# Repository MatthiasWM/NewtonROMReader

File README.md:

# NewtonROMReader

This archive contains the PCB layout and firmware source code for my Apple 
Newton MessagePad ROM board reader/programmer.

The Newton ROM Reader reads the contents of Apple MessagePad MP2x00 ROM
boards. Besides the well known US and German ROM, this programmer can read 
prototype ROM boards for further research.

Using the alternative Flash ROM Board, the ROM Reader can also program the
Flash chips and create new ROM Boards with patched or alternative 
operating systems. 

## CAUTION

 - Use an original Arduino Due. Do *NOT* use a Mega 2560!
 - Never insert or remove the ROM card while the programmer is powered!
 - All operations are final! There is no undo! There is no confirmation.

## Reader/Programmer

Assembling the Programmer requires some advanced soldering skills. The pin 
headers must be soldered around the outside of the board facing down. They 
must be flush with the PCB on the top, or the ROM board will not fit.

The SD Card connector is soldered to the underside of the board. The top
of the connector should be insulated using an ample amount of tape, avoiding
a short circuit with header pins on the Arduino. ALternatively, the colliding
pins on the Arduino board can be cut off.

The DIMM memory socket is more difficult to solder. The pin pitch is relatively
small. To make sure that the soldering is correct, the first tool to run
in the Programmer should be the short circuit test.

The last solder part is easy, but must not be forgotten. It's a jumper that 
sets the power to 3.2V. Connect the two eyes marked with an asterisk (*).

```
:
:   Lower left corner of the PCB
|
| ooo ooo
| ooo **o
|     ...... ........
+--------------------- - -
``` 

The Programmer board should be mounted on an Arduino Due. It *MUST NOT* be 
used with an Arduino Mega 1280/2560. The Mega runs at 5V and will likely
destroy any ROM, Flash, or SD card inserted into the Programmer. The Due runs
at the required 3.2V. If the large USB-A port of the Arduino blocks access to 
the SD Card slot, you have the wrong board!

The Programmer communicates with the user via USB connection to the Programming
port. No extra power connection is required. There is no extra software for
the Programmer. Users must use a serial terminal program to connect via the 
Programming USB port (57600 bps/baud 8N1).

## Firmware Source Code

The source code comes as an Arduino sketch `.ino` file and a number of 
additional source and header files. The "SdFat" library by Bill Greimann must be 
installed within the Arduino system `Tools > Manage Libraries...`.

Load the `.ino` file and set the board to `Arduino Due (Programming Port)`, 
then choose the right port from the `Tools > Port` menu.

Open the serial monitor `Tools > Serial Monitor` and press `Ctrl-U` to upload
the firmware to the Programmer.  

## PCB Layout

The Programmer PCB was designed with Eagle CAD 7.7.0 Stadard Edition. It's a
two layer board with no exeptional requirements.

The SO-DIMM 72 modules are not very common anymore and are somewhat hard to 
find. The SD Card socket is a standard SMD part. Pin headers should be 
square shaped to fit the Arduino receptacle well.

## Usage

The Programmer writes a 90's style menu over the USB serial port connection.
Functions can be selected by typing the command key and Return. 

 - `h`: Check all connectors on the board for short circuits. This tool helps
        verifying that there are no bridges in the SO DIMM connector soldering.
        *Never run this command with a ROM board or SD Card inserted!*
 - `0`: Select the ROM area from 0x00000000 to 0x00800000 which corresponds
        to the regular ROM and Apple system ROM extension (REx).
 - `1`: This page can be programmed with an extension block of up to 8MB.
 - `2`, `3`: Experimental blocks. These should be mapped to 0x10000000 and 
        can contain 8MB extensions each. This however is not yet verified.
 - `p`: Print the contents of the Flash as a hex dump with ASCII. Pressing 
        `return` will print the next block. Pressing any other key followed
        by `enter` will bring you back to the main menu. 
 - `c`: Check if the Flash memory is empty (all addresses return 0xFFFFFFFF).
 - `e`: Erase all sectors in the selected Flash area.
 - `w`: Write the content of a file on SD card or on an USB Drive to the 
        current Flash page. Filenames for pages 0 to 3 are set to "rom.bin",
        "rex1.bin", "rex2.bin", and "rex3.bin".
 - 'v': Verify the Flash content with the corresponding file on SD Card or 
        USB Drive.
  
## ToDo's

 - the SO DIMM footprint is really hard to solder, the pads are too big and 
   solder tends to short the pins
 - the LED can not be controlled because it is connected to a ROM Board output
 - address and data pins should be connected to 32 bit registers, making the 
   pin-by-pin addressing obsolete and the programmer much faster
 - the SPI port should be connected to a hardware SPI
 - there should be an option for a display and four buttons
 - the SD Card connecter must have pull-ups on most pins, and the Card 
   Detect and Write Protect pins should be connected to some pin

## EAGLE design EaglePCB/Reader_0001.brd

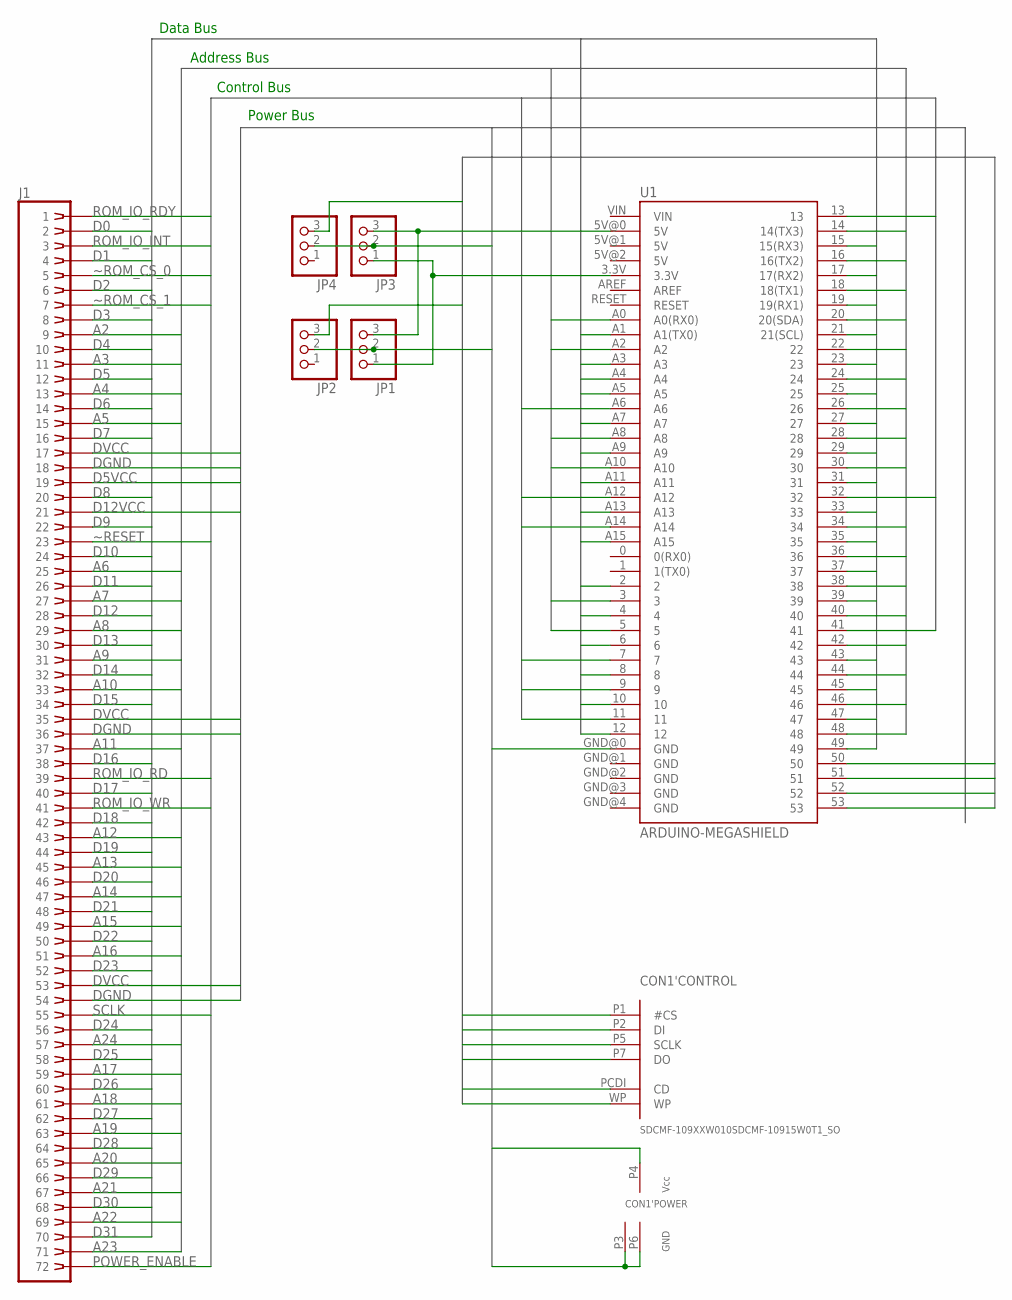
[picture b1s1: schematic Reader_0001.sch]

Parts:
CON1: SDCMF-109XXW010SDCMF-10915W0T1_SO; SDCMF-10915W0T1
J1: DIMM-M3; 177827-1
JP1, JP2, JP3, JP4: PINHD-1X3; 1X03
U1: ARDUINO-MEGASHIELD; ARDUINO_MEGA_SHIELD

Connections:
A2: J1.9, U1.5
A3: J1.11, U1.3
A4: J1.13, U1.A0 (A0(RX0))
A5: J1.15, U1.A2
A6: J1.25, U1.14 (14(TX3))
A7: J1.27, U1.16 (16(TX2))
A8: J1.29, U1.18 (18(TX1))
A9: J1.31, U1.20 (20(SDA))
A10: J1.33, U1.A8
A11: J1.37, U1.A10
A12: J1.43, U1.22
A13: J1.45, U1.24
A14: J1.47, U1.26
A15: J1.49, U1.28
A16: J1.51, U1.30
A17: J1.59, U1.36
A18: J1.61, U1.38
A19: J1.63, U1.40
A20: J1.65, U1.48
A21: J1.67, U1.46
A22: J1.69, U1.44
A23: J1.71, U1.42
A24: J1.57, U1.34
D0: J1.2, U1.12
D1: J1.4, U1.10
D2: J1.6, U1.8
D3: J1.8, U1.6
D4: J1.10, U1.4
D5: J1.12, U1.2
D5VCC: J1.19, JP1.2, JP2.2
D6: J1.14, U1.A1 (A1(TX0))
D7: J1.16, U1.A3
D8: J1.20, U1.A4
D9: J1.22, U1.A5
D10: J1.24, U1.A7
D11: J1.26, U1.15 (15(RX3))
D12: J1.28, U1.17 (17(RX2))
D12VCC: J1.21
D13: J1.30, U1.19 (19(RX1))
D14: J1.32, U1.21 (21(SCL))
D15: J1.34, U1.A9
D16: J1.38, U1.A11
D17: J1.40, U1.A13
D18: J1.42, U1.A15
D19: J1.44, U1.23
D20: J1.46, U1.25
D21: J1.48, U1.27
D22: J1.50, U1.29
D23: J1.52, U1.31
D24: J1.56, U1.33
D25: J1.58, U1.35
D26: J1.60, U1.37
D27: J1.62, U1.39
D28: J1.64, U1.49
D29: J1.66, U1.47
D30: J1.68, U1.45
D31: J1.70, U1.43
DGND: CON1.P3 (GND), CON1.P6 (GND), J1.18, J1.36, J1.54, U1.GND@0 (GND)
DVCC: CON1.P4 (VCC), J1.17, J1.35, J1.53, JP3.2, JP4.2
unnamed: JP1.3, JP3.3, U1.5V@0 (5V)
unnamed: JP1.1, JP3.1, U1.3.3V
POWER_ENABLE: J1.72, U1.41
ROM_IO_INT: J1.3, U1.11
ROM_IO_RD: J1.39, U1.A12
ROM_IO_RDY: J1.1, U1.13
ROM_IO_WR: J1.41, U1.A14
SCLK: J1.55, U1.32
SD_CD: CON1.PCDI (CD)
SD_CLCK: CON1.P5 (SCLK), U1.52
SD_CS: CON1.P1 (#CS), U1.53
SD_DI: CON1.P2 (DI), JP2.3, U1.51
SD_DO: CON1.P7 (DO), JP4.3, U1.50
SD_WP: CON1.WP
~RESET: J1.23, U1.A6
~ROM_CS_0: J1.5, U1.9
~ROM_CS_1: J1.7, U1.7

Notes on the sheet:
Data Bus
Address Bus
Control Bus
Power Bus

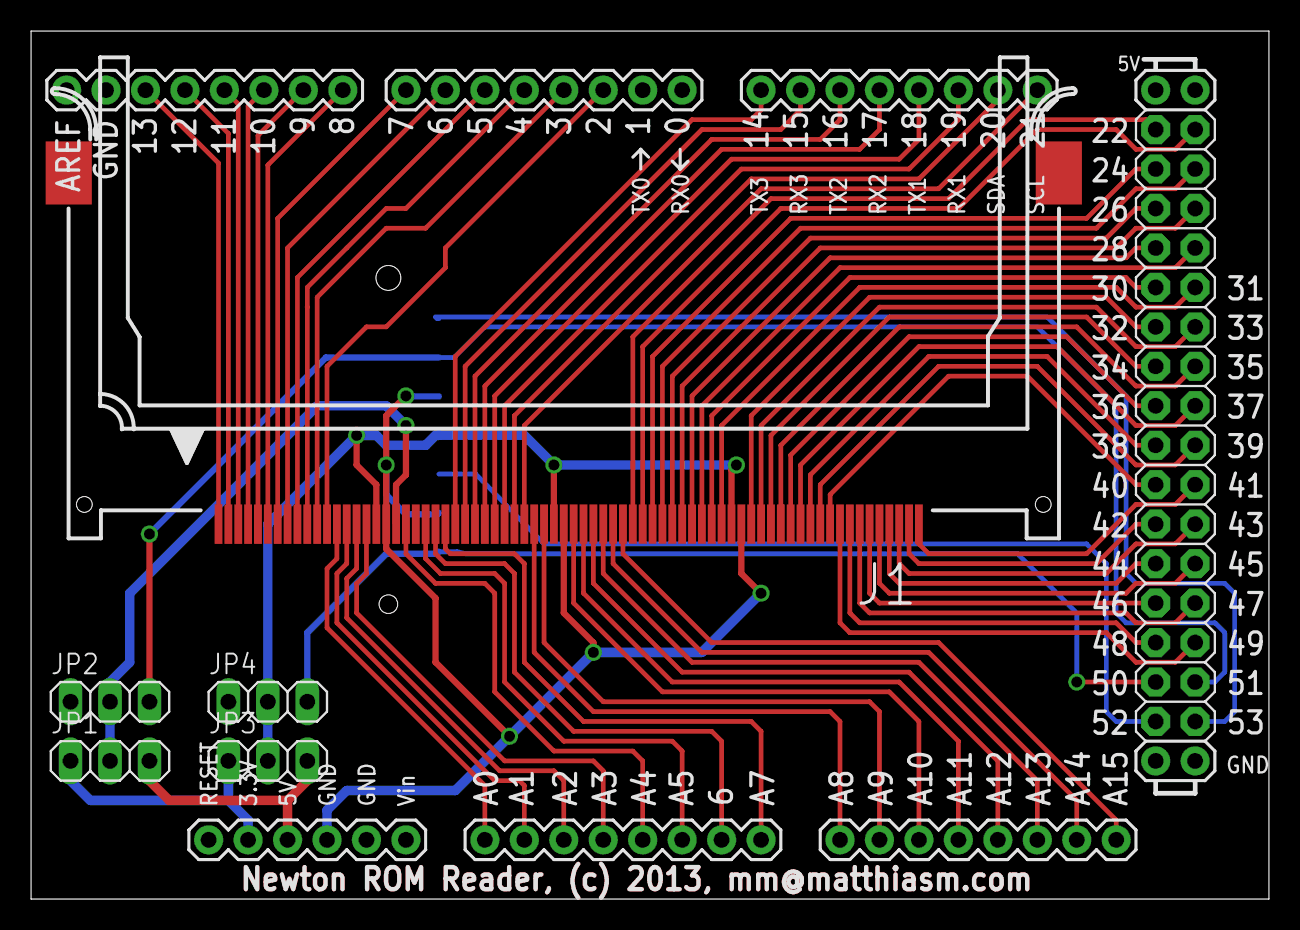
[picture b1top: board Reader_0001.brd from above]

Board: 2 copper layers, 79.7 x 55.9 mm, 7 parts (1 on the bottom side), 73 nets.

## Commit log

2022-03-01 Initial commmit
2022-03-02 Basic functionality
2022-03-02 Update docs
2022-03-02 Faster programming, faster reading, verify.
2022-03-09 Adding ROM Extension programming.
2022-03-11 More documentation within the source code.
2022-03-14 Fixed typos in README.md
2022-03-16 Many many changes
2022-03-16 typo
2022-03-16 more typos
2022-03-16 even more typos
2022-03-16 Experimenting with hidden pages.
2022-03-16 Accelerating ROM read by 35%
2022-03-17 Added function to copy ROM contents to SD card/USB stick.
2022-03-17 Fixed case in include file name
2022-03-17 Ignoring CR (\r) characters in the serial input
2022-03-27 A few typos in comments fixed
2022-04-06 Adding sample code for programming the board in situ.
2022-04-17 Getting structure going
2022-04-17 Added: Reading physical address.
2022-04-17 Working and tested: reading, writing word, erasing sector.
2022-04-17 Writing block, erase still crashes
2022-04-18 Working version, no sound
2022-04-18 Tested and working Rex writer.

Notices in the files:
EaglePCB/Reader_0001.brd:
Newton ROM Reader, (c) 2013, mm@matthiasm.com
parts and their libraries:
SparkFun-Boards: Licensing: CC v3.0 Share-Alike You are welcome to use this library for commercial purposes.
